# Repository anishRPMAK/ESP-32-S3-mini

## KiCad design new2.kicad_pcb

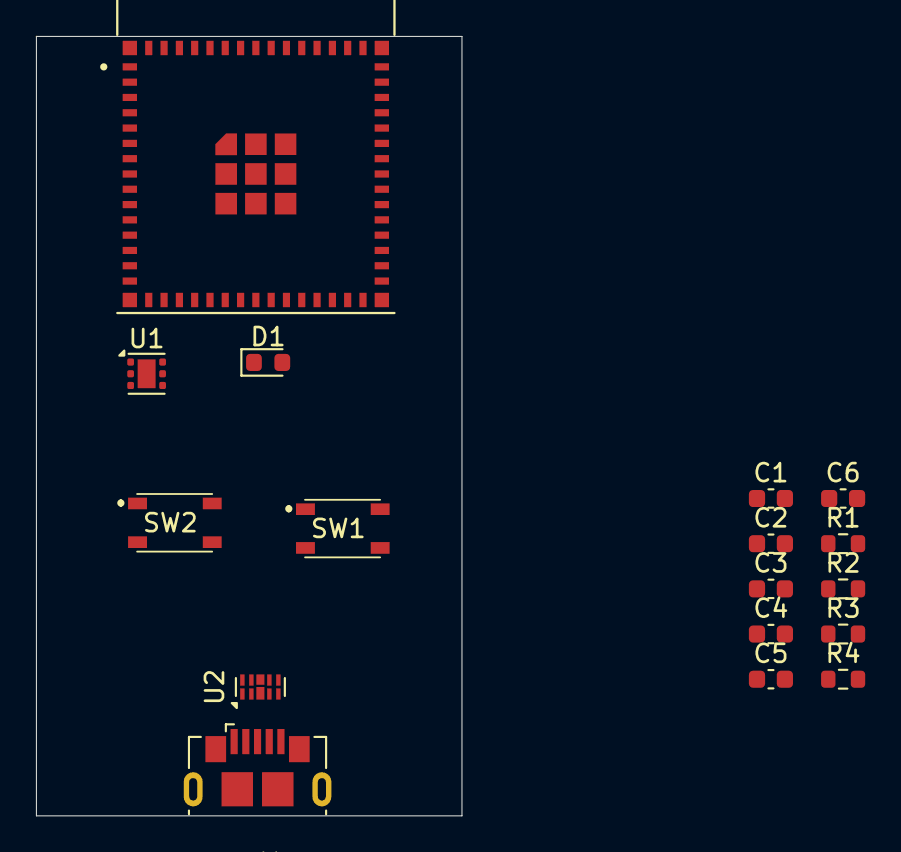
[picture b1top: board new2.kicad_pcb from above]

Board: 2 copper layers, 23.6 x 43.3 mm, 17 parts (0 on the bottom side), 10 nets, no tracks yet.

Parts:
C1, C2, C6: 10uF; C_0603_1608Metric
C3, C4, C5: 0.1uF; C_0603_1608Metric
D1: LED; LED_0603_1608Metric
J1: USB_B_Micro; USB_Micro-B_GCT_USB3076-30-A
R1: 1m; R_0603_1608Metric
R2: 200k; R_0603_1608Metric
R3: 5.1k; R_0603_1608Metric
R4: 10K; R_0603_1608Metric
SW1: BOOT1; PTS810SJG250SMTRLFS
SW2: RESET1; PTS810SJG250SMTRLFS
U1: TLV75801PDRV; WSON-6-1EP_2x2mm_P0.65mm_EP1x1.6mm
U2: D3V3XA4B10LP; Diodes_UDFN-10_1.0x2.5mm_P0.5mm
U3: ESP32-S3-MINI-1-N8; XCVR_ESP32-S3-MINI-1-N8

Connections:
/3V3: C2.1, C5.1, C6.1, R1.1, R3.1, R4.1, U1.1 (OUT), U3.3 (3V3)
/5VUSB: C1.1, J1.1 (VBUS), U1.4 (EN), U1.6 (IN), U2.4, U2.7 (NC)
/ESP32_EN: C3.1, R4.2, SW2.3 (K), SW2.4 (A), U3.45 (EN)
/GPIO0: C4.1, SW1.3 (K), SW1.4 (A), U3.4 (IO0)
/USB_B: J1.3 (D+), U2.2, U2.9 (NC), U3.24 (IO20)
/USB_N: J1.2 (D-), U2.1, U2.10 (NC), U3.23 (IO19)
GND: C3.2, C4.2, C5.2, C6.2, J1.5 (GND), J1.6 (Shield), SW1.1, SW1.2, SW2.1, SW2.2, U1.3 (GND), U1.7 (GND), U3.1 (GND), U3.2 (GND), U3.42 (GND), U3.43 (GND), U3.46 (GND), U3.47 (GND), U3.48 (GND), U3.49 (GND), U3.50 (GND), U3.51 (GND), U3.52 (GND), U3.53 (GND), U3.54 (GND), U3.55 (GND), U3.56 (GND), U3.57 (GND), U3.58 (GND), U3.59 (GND), U3.60 (GND), U3.61 (GND), U3.61_1 (GND), U3.61_2 (GND), U3.61_3 (GND), U3.61_4 (GND), U3.61_5 (GND), U3.61_6 (GND), U3.61_7 (GND), U3.61_8 (GND), U3.62 (GND), U3.63 (GND), U3.64 (GND), U3.65 (GND)
unnamed: D1.2 (A), R3.2
unnamed: C1.2, C2.2, D1.1 (K), R2.2
unnamed: R1.2, R2.1, U1.2 (FB)
